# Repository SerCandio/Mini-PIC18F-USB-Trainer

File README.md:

# Mini-PIC18F-USB-Trainer
Una versión de tamaño reducida a la ya dada en : https://github.com/SerCandio/Mini-PIC18F-TRAINER orientada a la instrumentación embebida

# Layouts
Podemos ver una version terminada de la tarjeta PCB a continuacion(elaborado en EAGLE - Fusion 360):

Figura 1.- Vista 3D en Fusion.

Mas vistas 3D: https://github.com/SerCandio/Mini-PIC18F-USB-Trainer/tree/main/3D%20Views

En este <a href="https://a360.co/3wHpknD">LINK</a> se puede visualizar una vista interactiva en tiempo real

# GERBER
Desde este link: https://github.com/SerCandio/Mini-PIC18F-USB-Trainer/tree/main/GERBER podemos descargar los archivos de fabricacion

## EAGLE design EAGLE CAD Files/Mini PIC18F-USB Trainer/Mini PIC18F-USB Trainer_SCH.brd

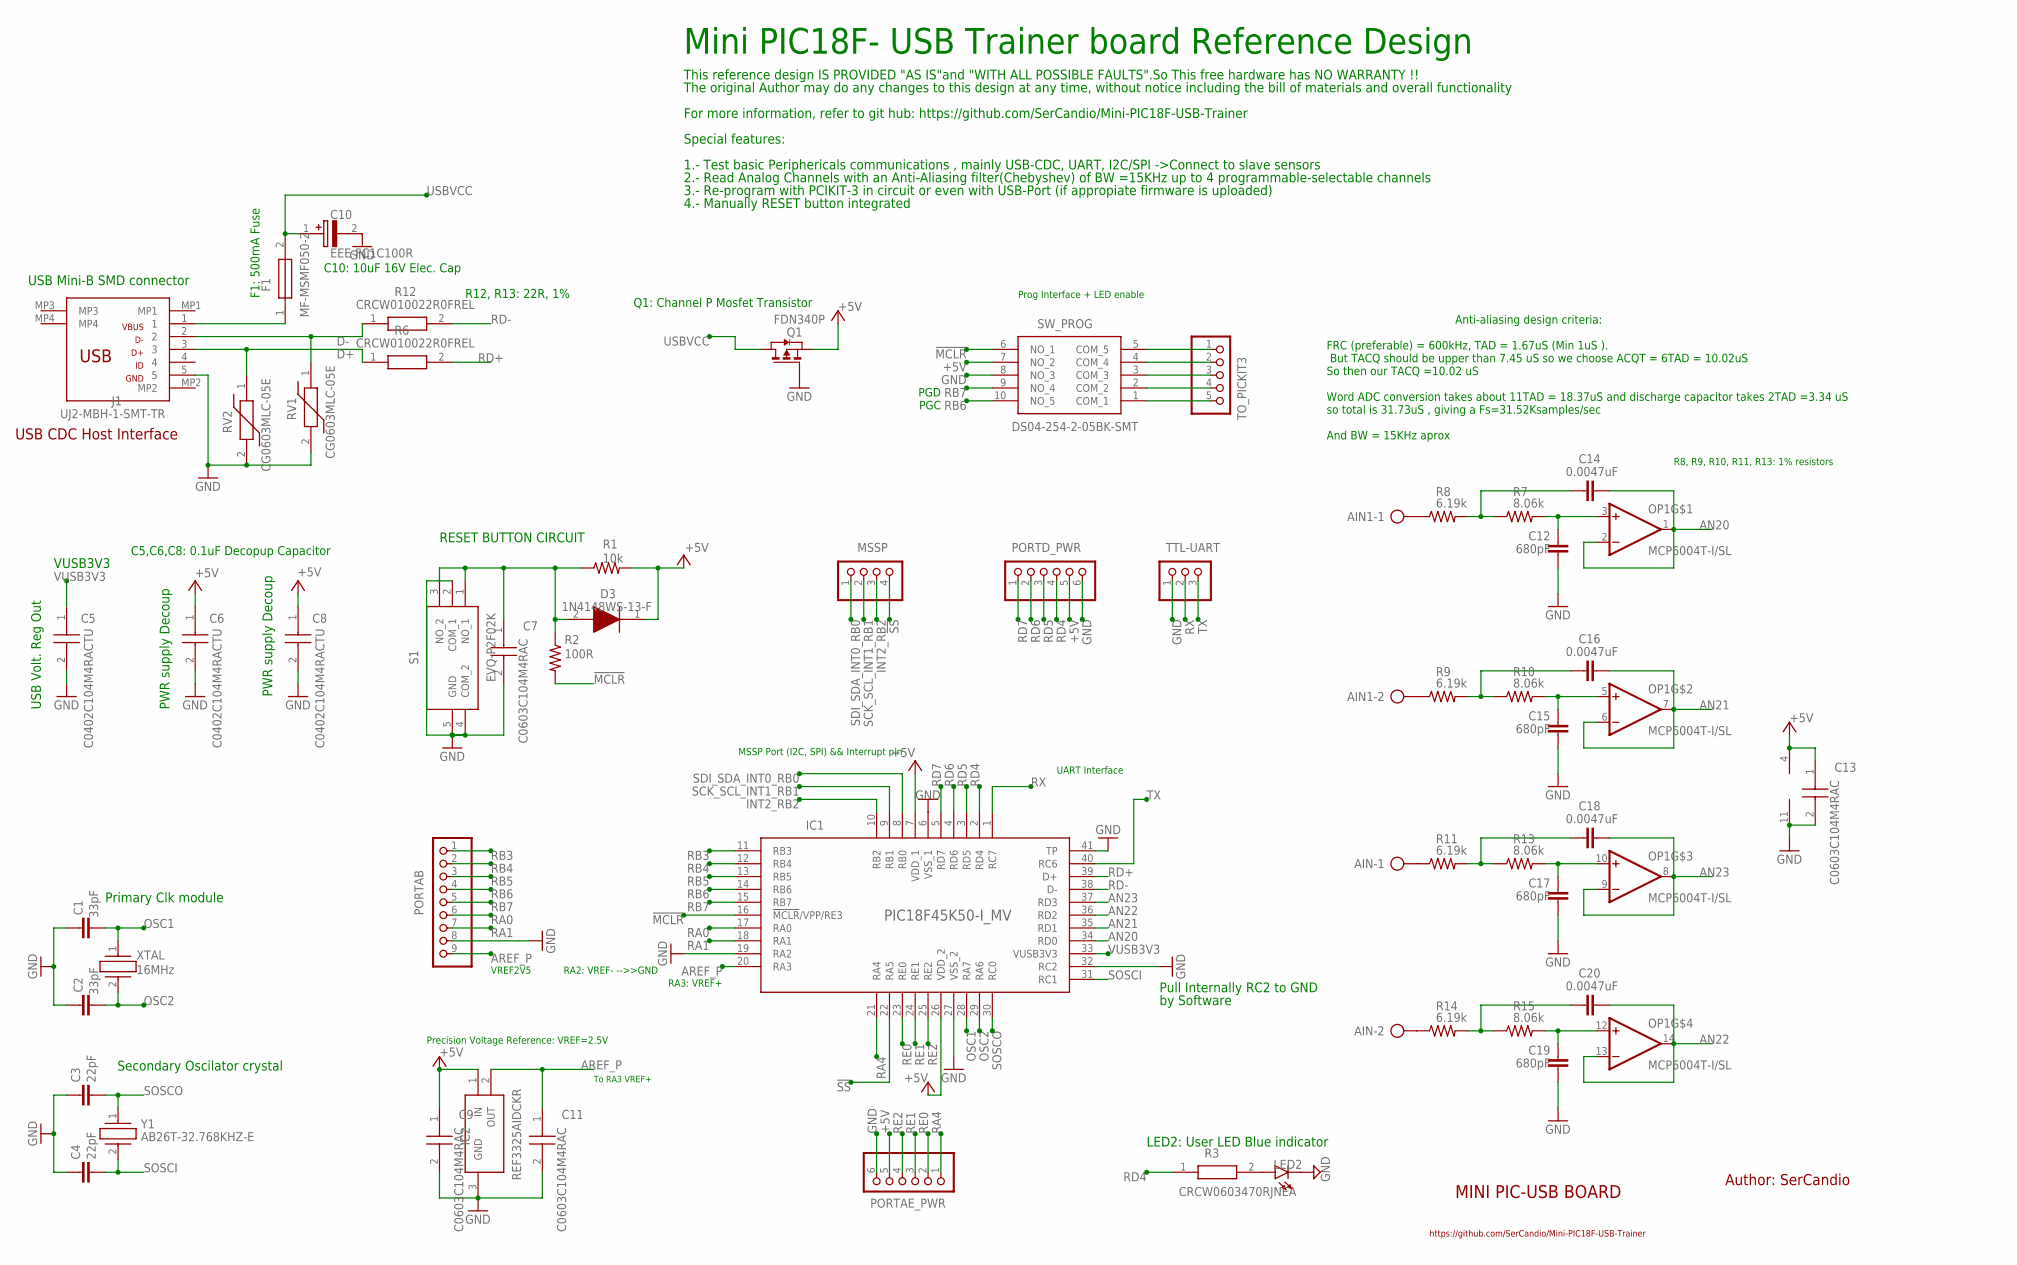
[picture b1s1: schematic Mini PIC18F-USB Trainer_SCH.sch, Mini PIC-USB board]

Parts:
AIN, AIN1: AK500/2-H
C1, C2: 33pF; C0603K; MANUFACTURER_PART_NUMBER 885012006020; MOUSER_PART_NUMBER 710-885012006020
C3, C4: 22pF; C0603K; MANUFACTURER_PART_NUMBER 0603YA220JAT2A; MOUSER_PART_NUMBER 581-0603YA220JAT2A
C5, C6, C8: C0402C104M4RACTU; C0402C104J4RACTU
C7, C9, C11, C13: C0603C104M4RAC; CAPC1608X95N
C10: EEE-FC1C100R; EEE1AA220WR
C12, C15, C17, C19: 680pF; C0603K; MANUFACTURER_PART_NUMBER 885012006028; MOUSER_PART_NUMBER 710-885012006028
C14, C16, C18, C20: 0.0047uF; C0603K; MANUFACTURER_PART_NUMBER VJ0603Y472JXJCW1BC; MOUSER_PART_NUMBER 77-VJ0603Y472JXJCBC
D3: 1N4148WS-13-F; SOD2513X120N
F1: MF-MSMF050-2; FUSC4632X85N
IC1: PIC18F45K50-I_MV; QFN40P500X500X55-41N
IC2: REF3325AIDCKR; SOT65P210X110-3N
J1: UJ2-MBH-1-SMT-TR; UJ2MBH1SMTTR
LED2: LEDCHIP-LED0805; CHIP-LED0805; MANUFACTURER_PART_NUMBER 150080BS75000; MOUSER_PART_NUMBER 710-150080BS75000
MSSP: PINHD-1X4; 1X04
OP1: MCP6004T-I/SL; SOIC127P600X175-14M
PORTAB: PINHD-1X9; 1X09
PORTAE_PWR: PINHD-1X6; 1X06
PORTD_PWR: PINHD-1X6; 1X06
Q1: FDN340P; SOT95P237X112-3N
R1: 10k; R0402; MANUFACTURER_PART_NUMBER CR0402-JW-103GLF; MOUSER_PART_NUMBER 652-CR0402-JW-103GLF
R2: 100R; R0402; MANUFACTURER_PART_NUMBER CR0402-JW-101GLF; MOUSER_PART_NUMBER 652-CR0402JW-101GLF
R3: CRCW0603470RJNEA; RESC1608X50N
R6, R12: CRCW010022R0FREL; RESC0402X15N
R7, R10, R13, R15: 8.06k; R0603; MANUFACTURER_PART_NUMBER CR0603-FX-8061ELF; MOUSER_PART_NUMBER 652-CR0603FX-8061ELF
R8, R9, R11, R14: 6.19k; R0603; MANUFACTURER_PART_NUMBER CR0603-FX-6191ELF; MOUSER_PART_NUMBER 652-CR0603FX-6191ELF
RV1, RV2: CG0603MLC-05E; VARC1608X55N
S1: EVQ-P2F02K; EVQP2V02W
SW_PROG: DS04-254-2-05BK-SMT; DS04254205BKSMT
TO_PICKIT3: PINHD-1X5/90; 1X05/90
TTL-UART: PINHD-1X3/90; 1X03/90
XTAL: 16MHz; LFXTAL020423CUTT
Y1: AB26T-32.768KHZ-E; AB26T32768KHZE

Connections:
!MCLR: IC1.16 (!MCLR!/VPP/RE3), R2.2, SW_PROG.6 (NO_1)
!SS: IC1.22 (RA5), MSSP.4
+5V: C6.1, C8.1, C9.1, C13.1, D3.1 (K), IC1.7 (VDD_1), IC1.26 (VDD_2), IC2.1 (IN), OP1.4 (V+), PORTAE_PWR.5, PORTD_PWR.5, Q1.2 (S), R1.2, SW_PROG.7 (NO_2)
AN20: C14.2, IC1.34 (RD0), OP1.1 (OUT), OP1.2 (-IN)
AN21: C16.2, IC1.35 (RD1), OP1.6 (-IN), OP1.7 (OUT)
AN22: C20.2, IC1.36 (RD2), OP1.13 (-IN), OP1.14 (OUT)
AN23: C18.2, IC1.37 (RD3), OP1.8 (OUT), OP1.9 (-IN)
AREF_P: C11.1, IC1.20 (RA3), IC2.2 (OUT), PORTAB.9
D+: J1.3, R6.1, RV2.1
D-: J1.2, R12.1, RV1.1
GND: C1.1, C2.1, C3.1, C4.1, C5.2, C6.2, C7.2, C8.2, C9.2, C10.2 (-), C11.2, C12.2, C13.2, C15.2, C17.2, C19.2, IC1.6 (VSS_1), IC1.19 (RA2), IC1.27 (VSS_2), IC1.32 (RC2), IC1.41 (TP), IC2.3 (GND), J1.5, LED2.C, OP1.11 (V-), PORTAB.8, PORTAE_PWR.6, PORTD_PWR.6, Q1.1 (G), RV1.2, RV2.2, S1.2 (COM_1), S1.4 (COM_2), S1.5 (GND), SW_PROG.8 (NO_3), TTL-UART.1
INT2_RB2: IC1.10 (RB2), MSSP.3
unnamed: SW_PROG.5 (COM_5), TO_PICKIT3.1
unnamed: C7.1, D3.2 (A), R1.1, R2.1, S1.1 (NO_1), S1.3 (NO_2)
unnamed: SW_PROG.4 (COM_4), TO_PICKIT3.2
unnamed: SW_PROG.3 (COM_3), TO_PICKIT3.3
unnamed: SW_PROG.2 (COM_2), TO_PICKIT3.4
unnamed: F1.1, J1.1
unnamed: AIN.1, R11.1
unnamed: SW_PROG.1 (COM_1), TO_PICKIT3.5
unnamed: LED2.A, R3.2
unnamed: AIN.2, R14.1
unnamed: C14.1, R7.1, R8.2
unnamed: C12.1, OP1.3 (+IN), R7.2
unnamed: AIN1.2, R9.1
unnamed: C16.1, R9.2, R10.1
unnamed: C15.1, OP1.5 (+IN), R10.2
unnamed: AIN1.1, R8.1
unnamed: C18.1, R11.2, R13.1
unnamed: C17.1, OP1.10 (+IN), R13.2
unnamed: C20.1, R14.2, R15.1
unnamed: C19.1, OP1.12 (+IN), R15.2
OSC1: C1.2, IC1.28 (RA7), XTAL.1
OSC2: C2.2, IC1.29 (RA6), XTAL.2
RA0: IC1.17 (RA0), PORTAB.6
RA1: IC1.18 (RA1), PORTAB.7
RA4: IC1.21 (RA4), PORTAE_PWR.1
RB3: IC1.11 (RB3), PORTAB.1
RB4: IC1.12 (RB4), PORTAB.2
RB5: IC1.13 (RB5), PORTAB.3
RB6: IC1.14 (RB6), PORTAB.4, SW_PROG.10 (NO_5)
RB7: IC1.15 (RB7), PORTAB.5, SW_PROG.9 (NO_4)
RD4: IC1.2 (RD4), PORTD_PWR.4, R3.1
RD5: IC1.3 (RD5), PORTD_PWR.3
RD6: IC1.4 (RD6), PORTD_PWR.2
RD7: IC1.5 (RD7), PORTD_PWR.1
RD+: IC1.39 (D+), R6.2
RD-: IC1.38 (D-), R12.2
RE0: IC1.23 (RE0), PORTAE_PWR.2
RE1: IC1.24 (RE1), PORTAE_PWR.3
RE2: IC1.25 (RE2), PORTAE_PWR.4
RX: IC1.1 (RC7), TTL-UART.2
SCK_SCL_INT1_RB1: IC1.9 (RB1), MSSP.2
SDI_SDA_INT0_RB0: IC1.8 (RB0), MSSP.1
SOSCI: C4.2, IC1.31 (RC1), Y1.2
SOSCO: C3.2, IC1.30 (RC0), Y1.1
TX: IC1.40 (RC6), TTL-UART.3
USBVCC: C10.1 (+), F1.2, Q1.3 (D)
VUSB3V3: C5.1, IC1.33 (VUSB3V3)

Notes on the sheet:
RESET BUTTON CIRCUIT
VUSB3V3
PWR supply Decoup
USB Volt. Reg Out
Primary Clk module
Secondary Oscilator crystal
USB Mini-B SMD connector
C10: 10uF 16V Elec. Cap
USB CDC Host Interface
F1: 500mA Fuse
Q1: Channel P Mosfet Transistor
RA2: VREF- -->>GND
RA3: VREF+
Prog Interface + LED enable
PGD
PGC
LED2: User LED Blue indicator
Precision Voltage Reference: VREF=2.5V
To RA3 VREF+
FRC (preferable) = 600kHz, TAD = 1.67uS (Min 1uS ).
But TACQ should be upper than 7.45 uS so we choose ACQT = 6TAD = 10.02uS
So then our TACQ =10.02 uS
Word ADC conversion takes about 11TAD = 18.37uS and discharge capacitor takes 2TAD =3.34 uS
so total is 31.73uS , giving a Fs=31.52Ksamples/sec
And BW = 15KHz aprox
Anti-aliasing design criteria:
MSSP Port (I2C, SPI) && Interrupt pin
UART Interface
R12, R13: 22R, 1%
C5,C6,C8: 0.1uF Decopup Capacitor
R8, R9, R10, R11, R13: 1% resistors
VREF2V5
Mini PIC18F- USB Trainer board Reference Design
This reference design IS PROVIDED "AS IS"and "WITH ALL POSSIBLE FAULTS".So This free hardware has NO WARRANTY !!
Special features:
1.- Test basic Periphericals communications , mainly USB-CDC, UART, I2C/SPI ->Connect to slave sensors
2.- Read Analog Channels with an Anti-Aliasing filter(Chebyshev) of BW =15KHz up to 4 programmable-selectable channels
3.- Re-program with PCIKIT-3 in circuit or even with USB-Port (if appropiate firmware is uploaded)
4.- Manually RESET button integrated
The original Author may do any changes to this design at any time, without notice including the bill of materials and overall functionality

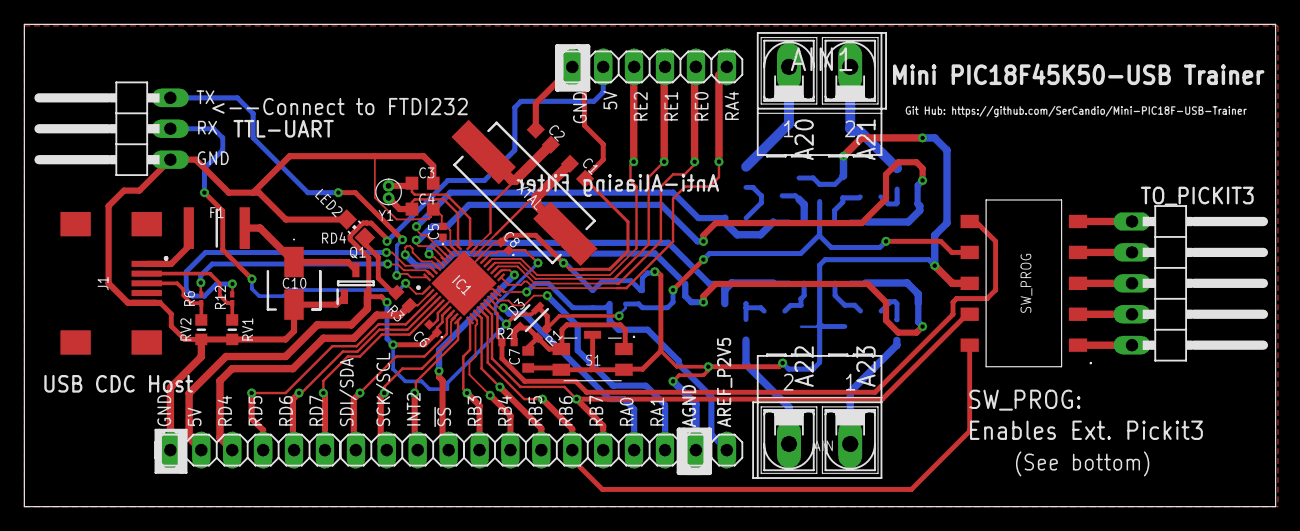
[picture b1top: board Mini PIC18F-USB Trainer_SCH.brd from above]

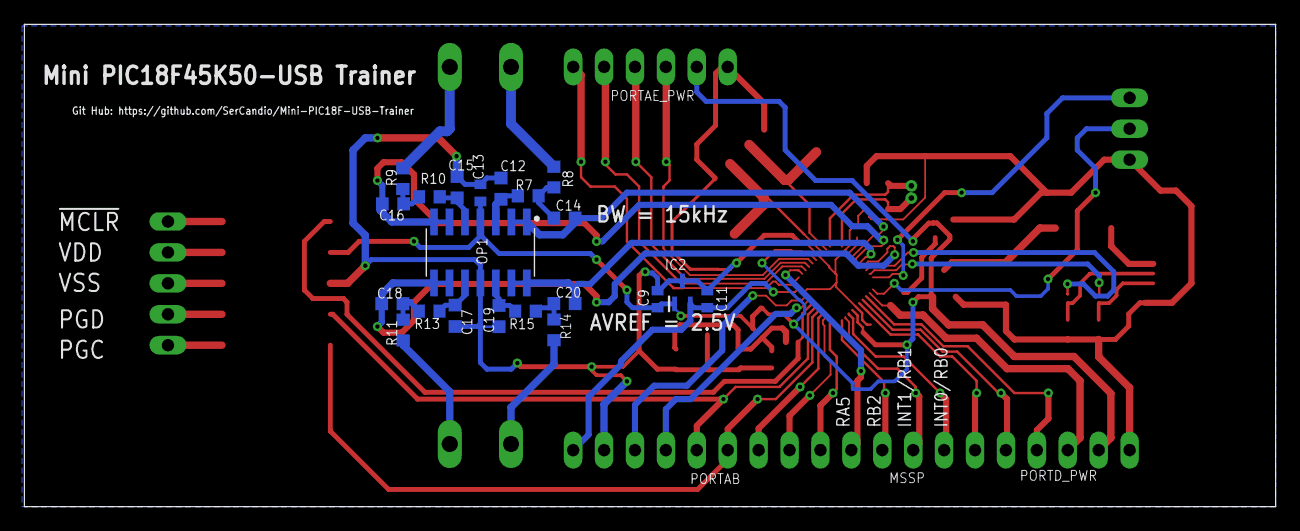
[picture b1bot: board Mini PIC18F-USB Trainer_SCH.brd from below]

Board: 2 copper layers, 102.8 x 39.6 mm, 55 parts (21 on the bottom side), 59 nets.

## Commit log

2024-03-04 EAGLE CAD Files
